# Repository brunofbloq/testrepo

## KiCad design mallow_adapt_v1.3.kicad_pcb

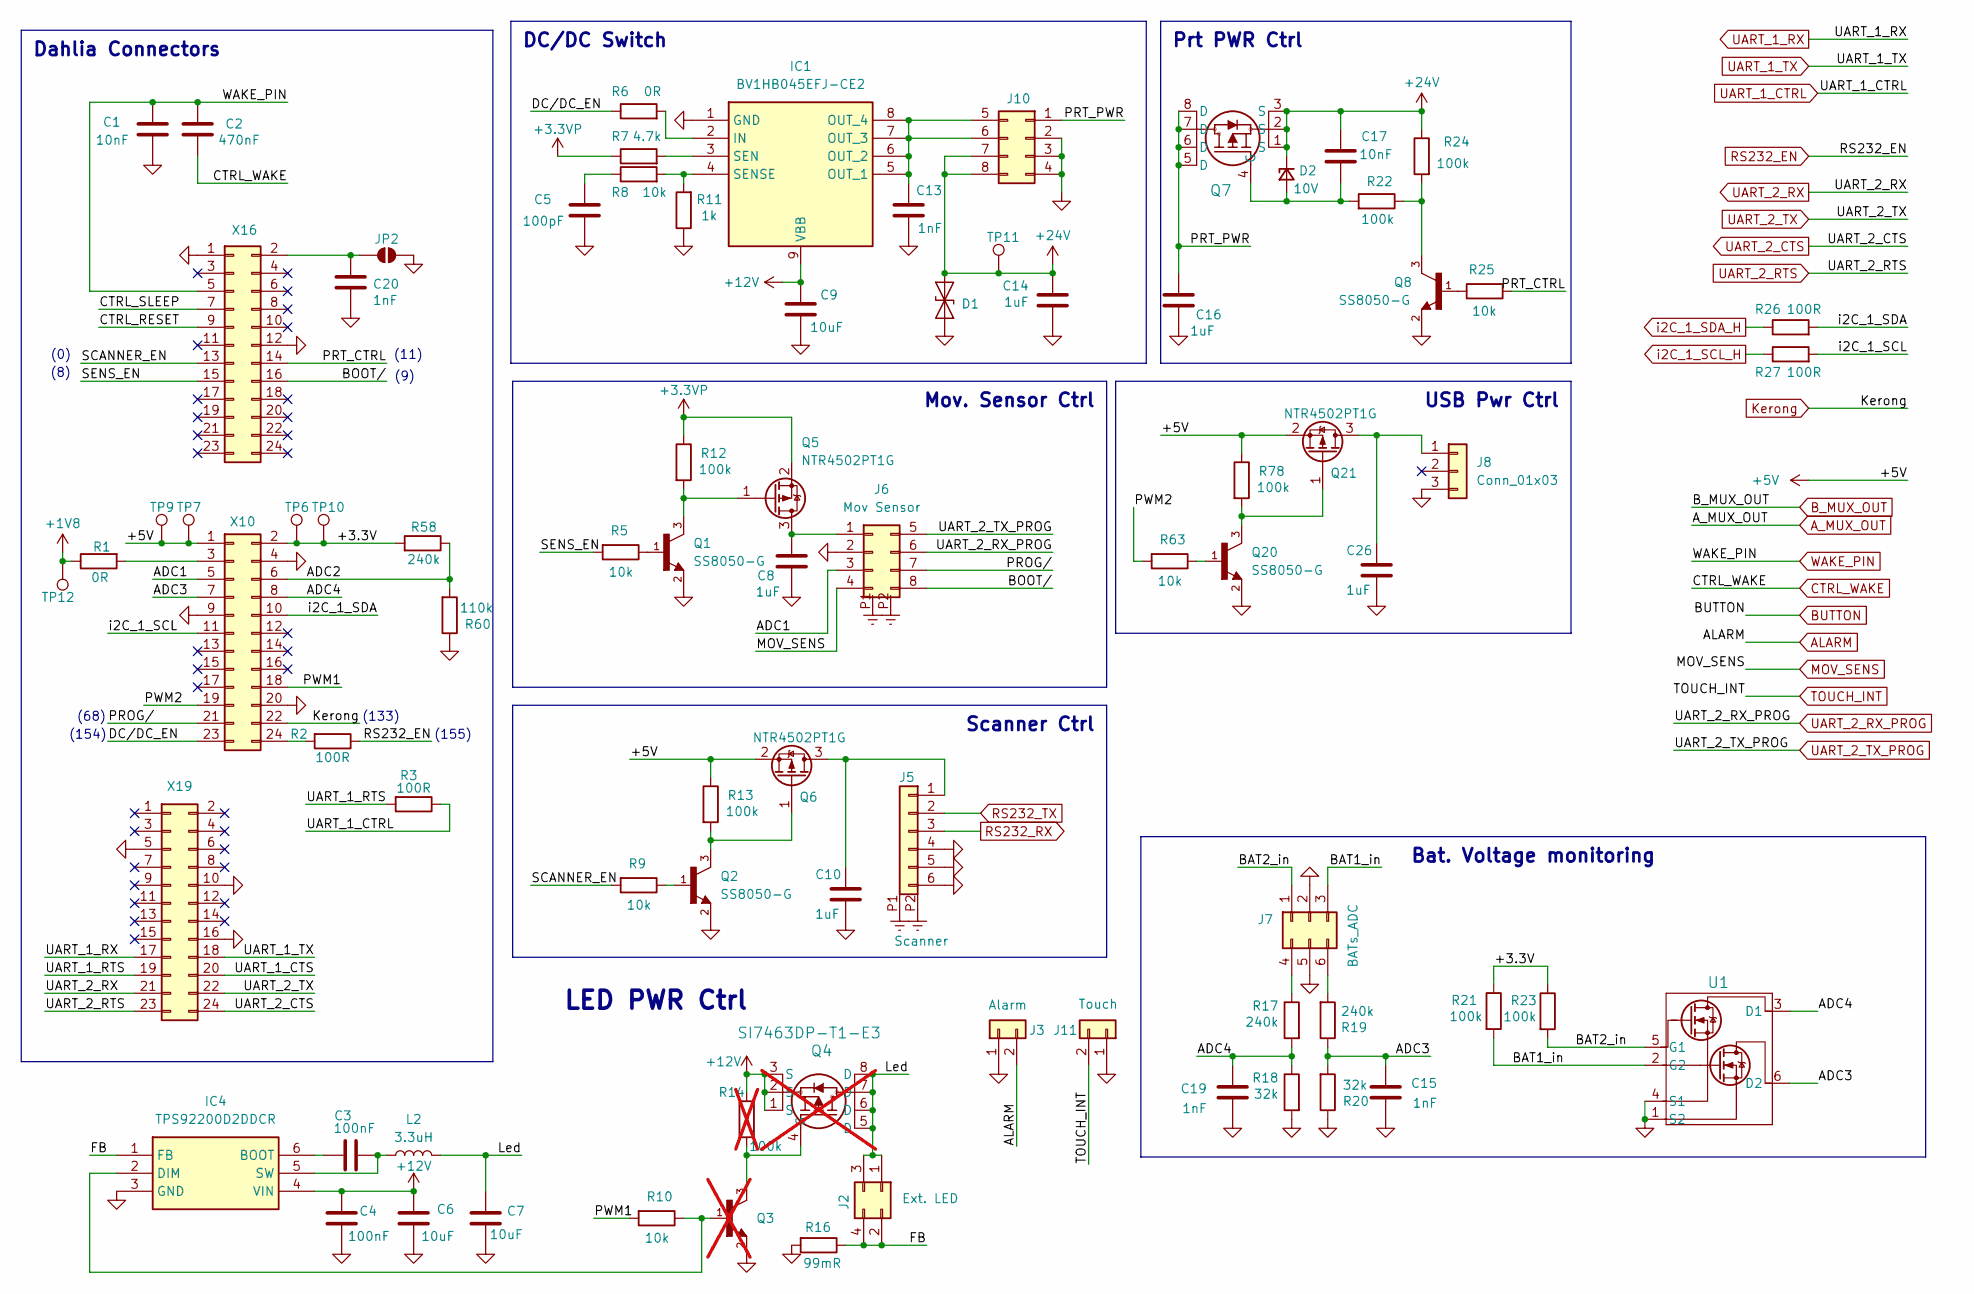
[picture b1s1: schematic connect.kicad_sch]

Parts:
C1, C17: 10nF; C_0603_1608Metric
C2: 470nF; C_0603_1608Metric
C3, C4: 100nF; C_0603_1608Metric
C5: 100pF; C_0603_1608Metric
C6, C7, C9: 10uF; C_0805_2012Metric
C8, C10, C16, C26: 1uF; C_0603_1608Metric
C13, C15, C19, C20: 1nF; C_0603_1608Metric
C14: 1uF; C_0805_2012Metric
D1: SMAJ24CA; D_SMA
D2: 10V; D_SOD-323_HandSoldering
IC1: BV1HB045EFJ-CE2; SOIC127P600X100-9N; Manufacturer_Part_Number BV1HB045EFJ-CE2
IC4: TPS92200D2DDCR; SOT95P280X110-6N; Manufacturer_Part_Number TPS92200D2DDCR
J2: Ext. LED; 1053101104
J3: Alarm; 1053091202
J5: Scanner; CON_430450624_MOL
J6: Mov Sensor; CON_1053121108
J7: BATs_ADC; CON_1053101106
J8: Conn_01x03; 1053091203
J10: 46015-0803
J11: Touch; Molex_PicoBlade_53048-0210_1x02_P1.25mm_Horizontal
JP2: Recovery; SolderJumper-2_P1.3mm_Open_RoundedPad1.0x1.5mm
L2: 3.3uH; L_1210_3225Metric
Q1, Q2, Q8, Q20: SS8050-G; TRANS_SS8050-G; PARTREV A
Q3: SS8050-G; TRANS_SS8050-G; PARTREV A; not fitted
Q4: SI7463DP-T1-E3; MOSFET_65DP-T1-E3_VIS; not fitted
Q5, Q6, Q21: NTR4502PT1G; SOT96P237X111-3N
Q7: SI7463DP-T1-E3; MOSFET_65DP-T1-E3_VIS
R1, R6: 0R; R_0603_1608Metric
R2, R3, R26, R27: 100R; R_0603_1608Metric
R5, R8, R9, R10, R25, R63: 10k; R_0603_1608Metric
R7: 4.7k; R_0603_1608Metric
R11: 1k; R_0603_1608Metric
R12, R13, R21, R22, R23, R24, R78: 100k; R_0603_1608Metric
R14: 100k; R_0603_1608Metric; not fitted
R16: 99mR; R_0805_2012Metric
R17, R19, R58: 240k; R_0603_1608Metric
R18, R20: 32k; R_0603_1608Metric
R60: 110k; R_0603_1608Metric
TP6, TP7, TP9, TP10, TP11, TP12: TestPoint; TestPoint_Pad_D2.0mm
U1: DMN53D0LDW-7; SOT-363_DIO
X10, X16, X19: Conn_02x12_Odd_Even; PinHeader_2x12_P2.54mm_Vertical

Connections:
+1V8: R1.1, TP12.1; also elsewhere on the board
+3.3VP: Q5.2 (S), R7.1, R12.1; also elsewhere on the board
+5V: Q6.2 (S), Q21.2 (S), R13.1, R78.1, TP7.1, TP9.1, X10.1
+12V: C4.1, C6.1, C9.1, IC1.9 (VBB), IC4.4 (VIN), Q4.1 (S), Q4.2 (S), Q4.3 (S), R14.1; also elsewhere on the board
+24V: C14.1, C17.1, D1.2 (A2), D2.1 (K), J10.7, J10.8, Q7.1 (S), Q7.2 (S), Q7.3 (S), R24.1, TP11.1; also elsewhere on the board
/Connectors/+3.3V: R21.1, R23.1, R58.2, TP6.1, TP10.1, X10.2
/Connectors/ADC1: J6.3, X10.5
/Connectors/ADC2: R58.1, R60.2, X10.6
/Connectors/ADC3: C15.1, R19.1, R20.2, U1.6 (D2), X10.7
/Connectors/ADC4: C19.1, R17.2, R18.1, U1.3 (D1), X10.8
/Connectors/BAT1_in: J7.3, R21.2, U1.2 (G2)
/Connectors/BAT2_in: J7.1, R23.2, U1.5 (G1)
/Connectors/BOOT/: J6.8, X16.16
/Connectors/CTRL_RESET: X16.9
/Connectors/CTRL_SLEEP: X16.7
/Connectors/DC/DC_EN: R6.1, X10.23
/Connectors/FB: IC4.1 (FB), J2.2, J2.4, R16.1
/Connectors/Led: C7.1, J2.1, J2.3, L2.2, Q4.5 (D), Q4.6 (D), Q4.7 (D), Q4.8 (D)
/Connectors/PROG/: J6.7, X10.21
/Connectors/PRT_CTRL: R25.2, X16.14
/Connectors/PRT_PWR: C16.1, J10.1, Q7.5 (D), Q7.6 (D), Q7.7 (D), Q7.8 (D)
/Connectors/PWM1: R10.2, X10.18
/Connectors/PWM2: R63.2, X10.19
/Connectors/SCANNER_EN: R9.2, X16.13
/Connectors/SENS_EN: R5.2, X16.15
/Connectors/UART_1_CTS: X19.20
/Connectors/UART_1_RTS: R3.2, X19.19
/Connectors/i2C_1_SCL: R27.2, X10.11
/Connectors/i2C_1_SDA: R26.2, X10.10
ALARM: J3.2; also elsewhere on the board
CTRL_WAKE: C2.2; also elsewhere on the board
GND: C1.2, C4.2, C5.2, C6.2, C7.2, C8.2, C9.2, C10.2, C13.2, C14.2, C15.2, C16.2, C19.2, C20.2, C26.2, D1.1 (A1), IC1.1 (GND), IC4.3 (GND), J3.1, J5.4, J5.5, J5.6, J6.2, J7.2, J7.5, J8.3, J10.2, J10.3, J10.4, J11.1, JP2.2 (B), Q1.2, Q2.2, Q3.2, Q8.2, Q20.2, R11.1, R16.2, R18.2, R20.1, R60.1, U1.1 (S2), U1.4 (S1), X10.4, X10.9, X10.20, X16.1, X16.12, X19.5, X19.10, X19.16; also elsewhere on the board
GND_CHASSIS: J5.P1 (Pin_6), J5.P2 (Pin_6), J6.P1 (Pin_8), J6.P2 (Pin_8); also elsewhere on the board
Kerong: X10.22; also elsewhere on the board
MOV_SENS: J6.4; also elsewhere on the board
unnamed: C5.1, R8.1
unnamed: C17.2, D2.2 (A), Q7.4 (G), R22.2
unnamed: IC1.2 (IN), R6.2
unnamed: C13.1, IC1.5 (OUT_1), IC1.6 (OUT_2), IC1.7 (OUT_3), IC1.8 (OUT_4), J10.5, J10.6
unnamed: IC1.3 (SEN), R7.2
unnamed: IC1.4 (SENSE), R8.2, R11.2
unnamed: C3.1, IC4.6 (BOOT)
unnamed: IC4.2 (DIM), Q3.1, R10.1
unnamed: C3.2, IC4.5 (SW), L2.1
unnamed: C10.1, J5.1, Q6.3 (D)
unnamed: C8.1, J6.1, Q5.3 (D)
unnamed: J7.4, R17.1
unnamed: J7.6, R19.2
unnamed: C26.1, J8.1, Q21.3 (D)
unnamed: C20.1, JP2.1 (A), X16.2
unnamed: Q1.1, R5.1
unnamed: Q2.1, R9.1
unnamed: Q3.3, Q4.4 (G), R14.2
unnamed: Q1.3, Q5.1 (G), R12.2
unnamed: Q2.3, Q6.1 (G), R13.2
unnamed: Q8.1, R25.1
unnamed: Q8.3, R22.1, R24.2
unnamed: Q20.1, R63.1
unnamed: Q20.3, Q21.1 (G), R78.2
unnamed: R1.2, X10.3
unnamed: R2.2, X10.24
RS232_EN: R2.1; also elsewhere on the board
RS232_RX: J5.3; also elsewhere on the board
RS232_TX: J5.2; also elsewhere on the board
TOUCH_INT: J11.2; also elsewhere on the board
UART_1_CTRL: R3.1; also elsewhere on the board
UART_1_RX: X19.17; also elsewhere on the board
UART_1_TX: X19.18; also elsewhere on the board
UART_2_CTS: X19.24; also elsewhere on the board
UART_2_RTS: X19.23; also elsewhere on the board
UART_2_RX: X19.21; also elsewhere on the board
UART_2_RX_PROG: J6.6; also elsewhere on the board
UART_2_TX: X19.22; also elsewhere on the board
UART_2_TX_PROG: J6.5; also elsewhere on the board
WAKE_PIN: C1.1, C2.1, X16.5; also elsewhere on the board
i2C_1_SCL_H: R27.1; also elsewhere on the board
i2C_1_SDA_H: R26.1; also elsewhere on the board

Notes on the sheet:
USB Pwr Ctrl
Dahlia Connectors
LED PWR Ctrl
Bat. Voltage monitoring
Scanner Ctrl
DC/DC Switch
Mov. Sensor Ctrl
Prt PWR Ctrl
(0)
(8)
(9)
(133)
(68)
(154)
(11)
(155)

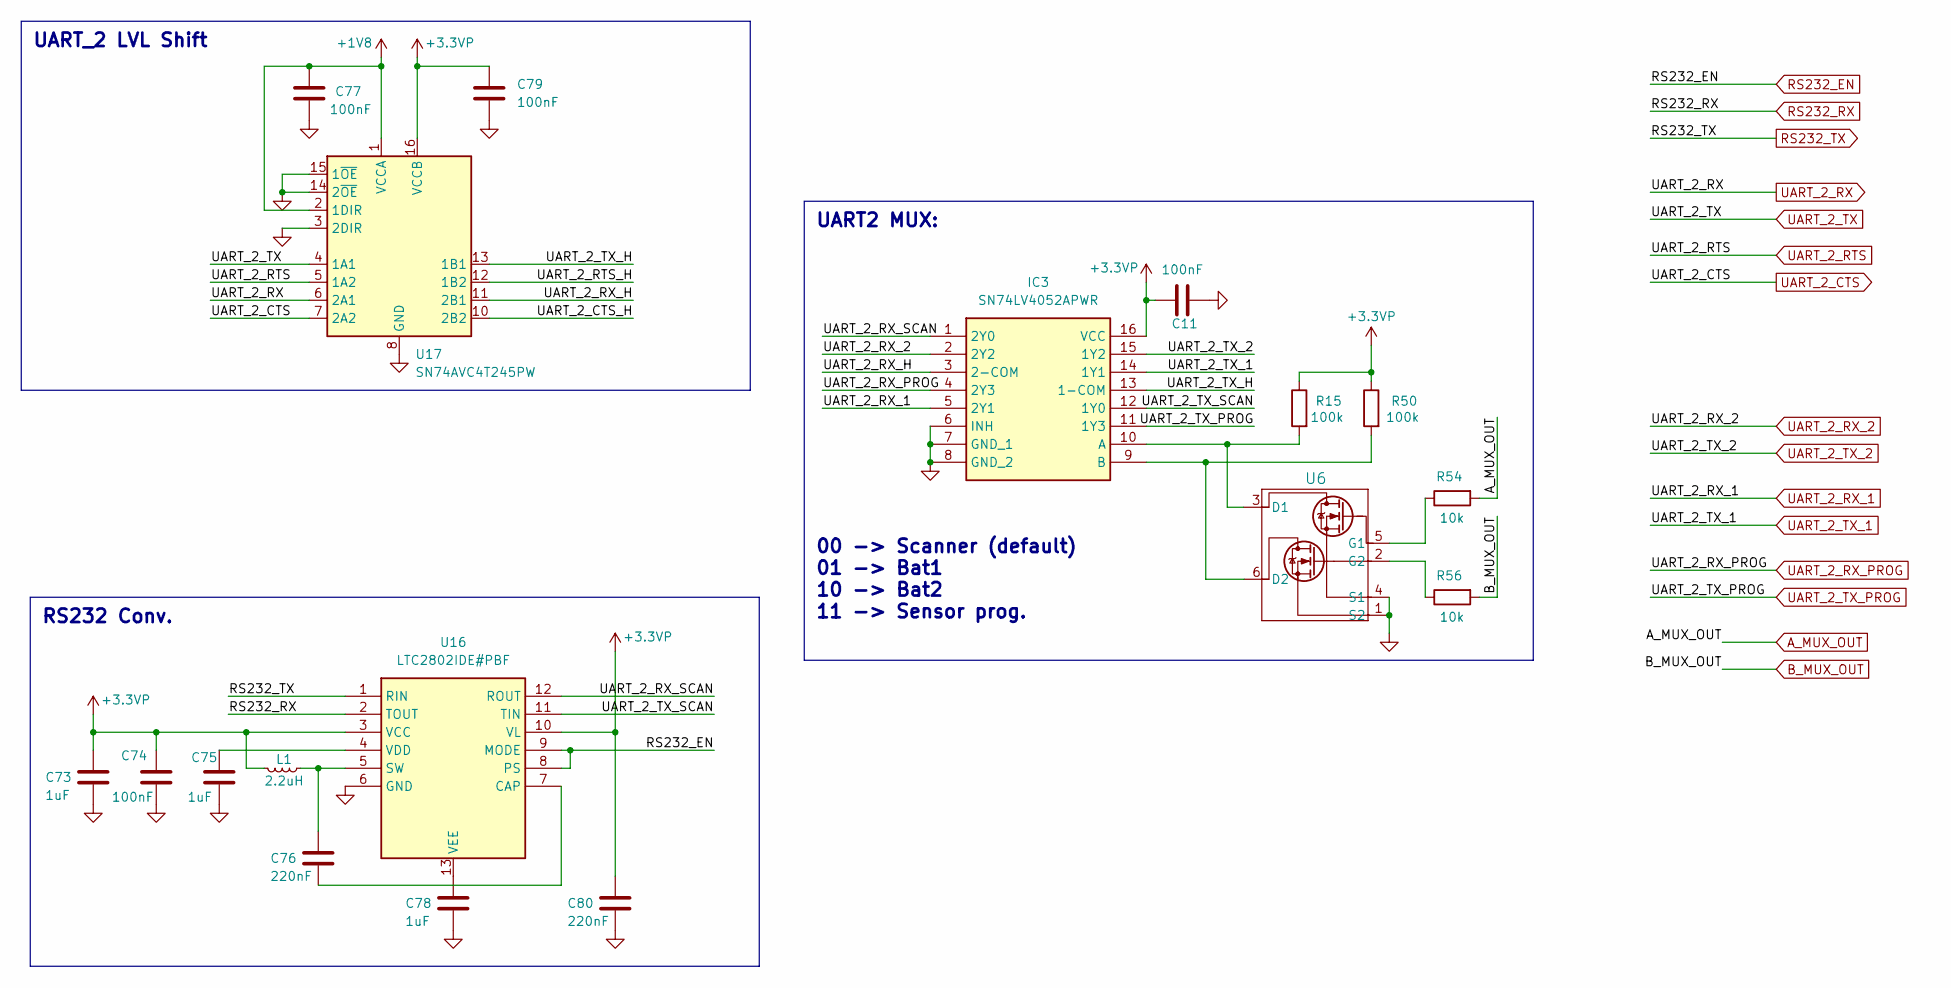
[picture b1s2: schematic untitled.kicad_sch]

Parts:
C11, C74, C77, C79: 100nF; C_0603_1608Metric
C73, C75, C78: 1uF; C_0603_1608Metric
C76, C80: 220nF; C_0603_1608Metric
IC3: SN74LV4052APWR; SOP65P640X120-16N; Manufacturer_Part_Number SN74LV4052APWR; Mouser Part Number 595-SN74LV4052APWR
L1: 2.2uH; L_0805_2012Metric
R15, R50: 100k; R_0603_1608Metric
R54, R56: 10k; R_0603_1608Metric
U6: DMN53D0LDW-7; SOT-363_DIO
U16: LTC2802IDE#PBF; LTC2802__SON50P300X400X80-13N-D; Manufacturer_Part_Number LTC2802IDE#PBF; Mouser Part Number 584-LTC2802IDE#PBF
U17: SN74AVC4T245PW; TSSOP-16_4.4x5mm_P0.65mm

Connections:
+1V8: C77.1, U17.1 (VCCA), U17.2 (1DIR); also elsewhere on the board
+3.3VP: C11.1, C73.1, C74.1, C79.1, C80.1, IC3.16 (VCC), L1.2, R15.1, R50.1, U16.3 (VCC), U16.10 (VL), U17.16 (VCCB); also elsewhere on the board
/UARTs/UART_2_CTS_H: U17.10 (2B2)
/UARTs/UART_2_RTS_H: U17.12 (1B2)
/UARTs/UART_2_RX_H: IC3.3 (2-COM), U17.11 (2B1)
/UARTs/UART_2_RX_SCAN: IC3.1 (2Y0), U16.12 (ROUT)
/UARTs/UART_2_TX_H: IC3.13 (1-COM), U17.13 (1B1)
/UARTs/UART_2_TX_SCAN: IC3.12 (1Y0), U16.11 (TIN)
A_MUX_OUT: R54.2; also elsewhere on the board
B_MUX_OUT: R56.2; also elsewhere on the board
GND: C11.2, C73.2, C74.2, C75.2, C77.2, C78.2, C79.2, C80.2, IC3.6 (INH), IC3.7 (GND_1), IC3.8 (GND_2), U6.1 (S2), U6.4 (S1), U16.6 (GND), U17.3 (2DIR), U17.8 (GND), U17.9 (GND), U17.14 (2~OE), U17.15 (1~OE); also elsewhere on the board
unnamed: IC3.10 (A), R15.2, U6.3 (D1)
unnamed: IC3.9 (B), R50.2, U6.6 (D2)
unnamed: R54.1, U6.5 (G1)
unnamed: R56.1, U6.2 (G2)
unnamed: C76.2, U16.7 (CAP)
unnamed: C76.1, L1.1, U16.5 (SW)
unnamed: C75.1, U16.4 (VDD)
unnamed: C78.1, U16.13 (VEE)
RS232_EN: U16.8 (PS), U16.9 (MODE); also elsewhere on the board
RS232_RX: U16.2 (TOUT); also elsewhere on the board
RS232_TX: U16.1 (RIN); also elsewhere on the board
UART_2_CTS: U17.7 (2A2); also elsewhere on the board
UART_2_RTS: U17.5 (1A2); also elsewhere on the board
UART_2_RX: U17.6 (2A1); also elsewhere on the board
UART_2_RX_1: IC3.5 (2Y1); also elsewhere on the board
UART_2_RX_2: IC3.2 (2Y2); also elsewhere on the board
UART_2_RX_PROG: IC3.4 (2Y3); also elsewhere on the board
UART_2_TX: U17.4 (1A1); also elsewhere on the board
UART_2_TX_1: IC3.14 (1Y1); also elsewhere on the board
UART_2_TX_2: IC3.15 (1Y2); also elsewhere on the board
UART_2_TX_PROG: IC3.11 (1Y3); also elsewhere on the board

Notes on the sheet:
UART_2 LVL Shift
RS232 Conv.
UART2 MUX: 00 -> Scanner (default) 01 -> Bat1 10 -> Bat2 11 -> Sensor prog.

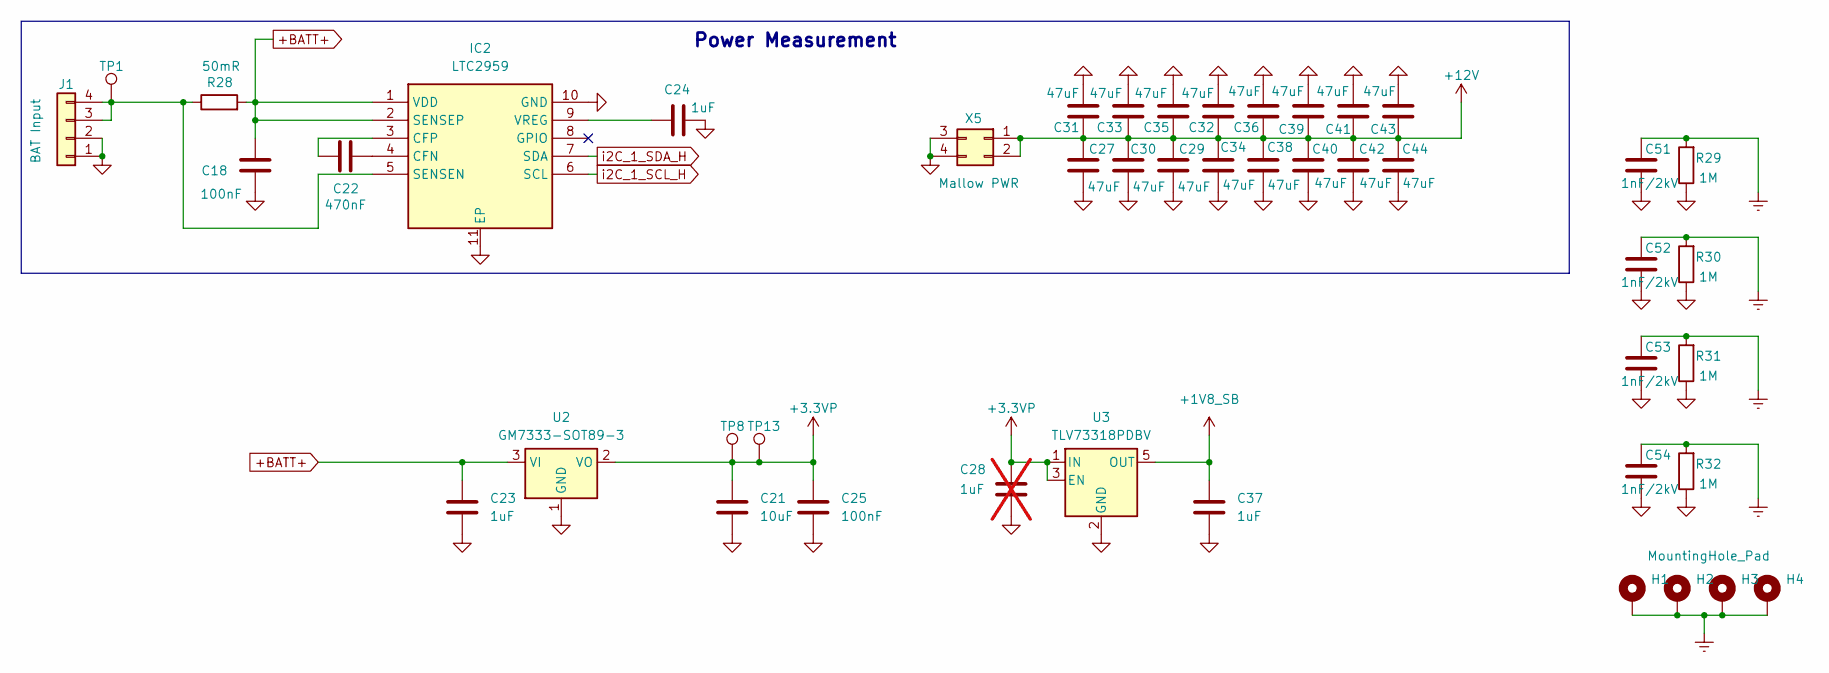
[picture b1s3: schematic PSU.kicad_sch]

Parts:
C18, C25: 100nF; C_0603_1608Metric
C21: 10uF; C_0603_1608Metric
C22: 470nF; C_0603_1608Metric
C23, C24, C37: 1uF; C_0603_1608Metric
C27, C29, C30, C31, C32, C33, C34, C35, C36, C38, C39, C40, C41, C42, C43, C44: 47uF; C_1210_3225Metric
C28: 1uF; C_0603_1608Metric; not fitted
C51, C52, C53, C54: 1nF/2kV; C_1206_3216Metric
H1, H2, H3, H4: MountingHole_Pad; MountingHole_3.2mm_M3_ISO7380_Pad_TopBottom
IC2: LTC2959; SON50P200X300X80-11N-D; Manufacturer_Part_Number LTC2959; Mouser Part Number N/A
J1: BAT Input; 46015-0403
R28: 50mR; R_2512_6332Metric
R29, R30, R31, R32: 1M; R_1206_3216Metric
TP1, TP8, TP13: TestPoint; TestPoint_Pad_D2.0mm
U2: GM7333-SOT89-3; SOT-89-3
U3: TLV73318PDBV; SOT-23-5
X5: Mallow PWR; PinHeader_2x02_P2.54mm_Vertical

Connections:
+1V8_SB: C37.1, U3.5 (OUT); also elsewhere on the board
+3.3VP: C21.1, C25.1, C28.1, TP8.1, TP13.1, U2.2 (VO), U3.1 (IN), U3.3 (EN); also elsewhere on the board
+12V: C27.1, C29.1, C30.1, C31.1, C32.1, C33.1, C34.1, C35.1, C36.1, C38.1, C39.1, C40.1, C41.1, C42.1, C43.1, C44.1, X5.1, X5.2; also elsewhere on the board
+BATT+: C18.1, C23.1, IC2.1 (VDD), IC2.2 (SENSEP), R28.2, U2.3 (VI); also elsewhere on the board
GND: C18.2, C21.2, C23.2, C24.2, C25.2, C27.2, C28.2, C29.2, C30.2, C31.2, C32.2, C33.2, C34.2, C35.2, C36.2, C37.2, C38.2, C39.2, C40.2, C41.2, C42.2, C43.2, C44.2, C51.2, C52.2, C53.2, C54.2, IC2.10 (GND), IC2.11 (EP), J1.1, J1.2, R29.1, R30.1, R31.1, R32.1, U2.1 (GND), U3.2 (GND), X5.3, X5.4; also elsewhere on the board
GND_CHASSIS: C51.1, C52.1, C53.1, C54.1, H1.1, H2.1, H3.1, H4.1, R29.2, R30.2, R31.2, R32.2; also elsewhere on the board
unnamed: C22.2, IC2.4 (CFN)
unnamed: C22.1, IC2.3 (CFP)
unnamed: IC2.5 (SENSEN), J1.3, J1.4, R28.1, TP1.1
unnamed: C24.1, IC2.9 (VREG)
i2C_1_SCL_H: IC2.6 (SCL); also elsewhere on the board
i2C_1_SDA_H: IC2.7 (SDA); also elsewhere on the board

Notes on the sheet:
Power Measurement

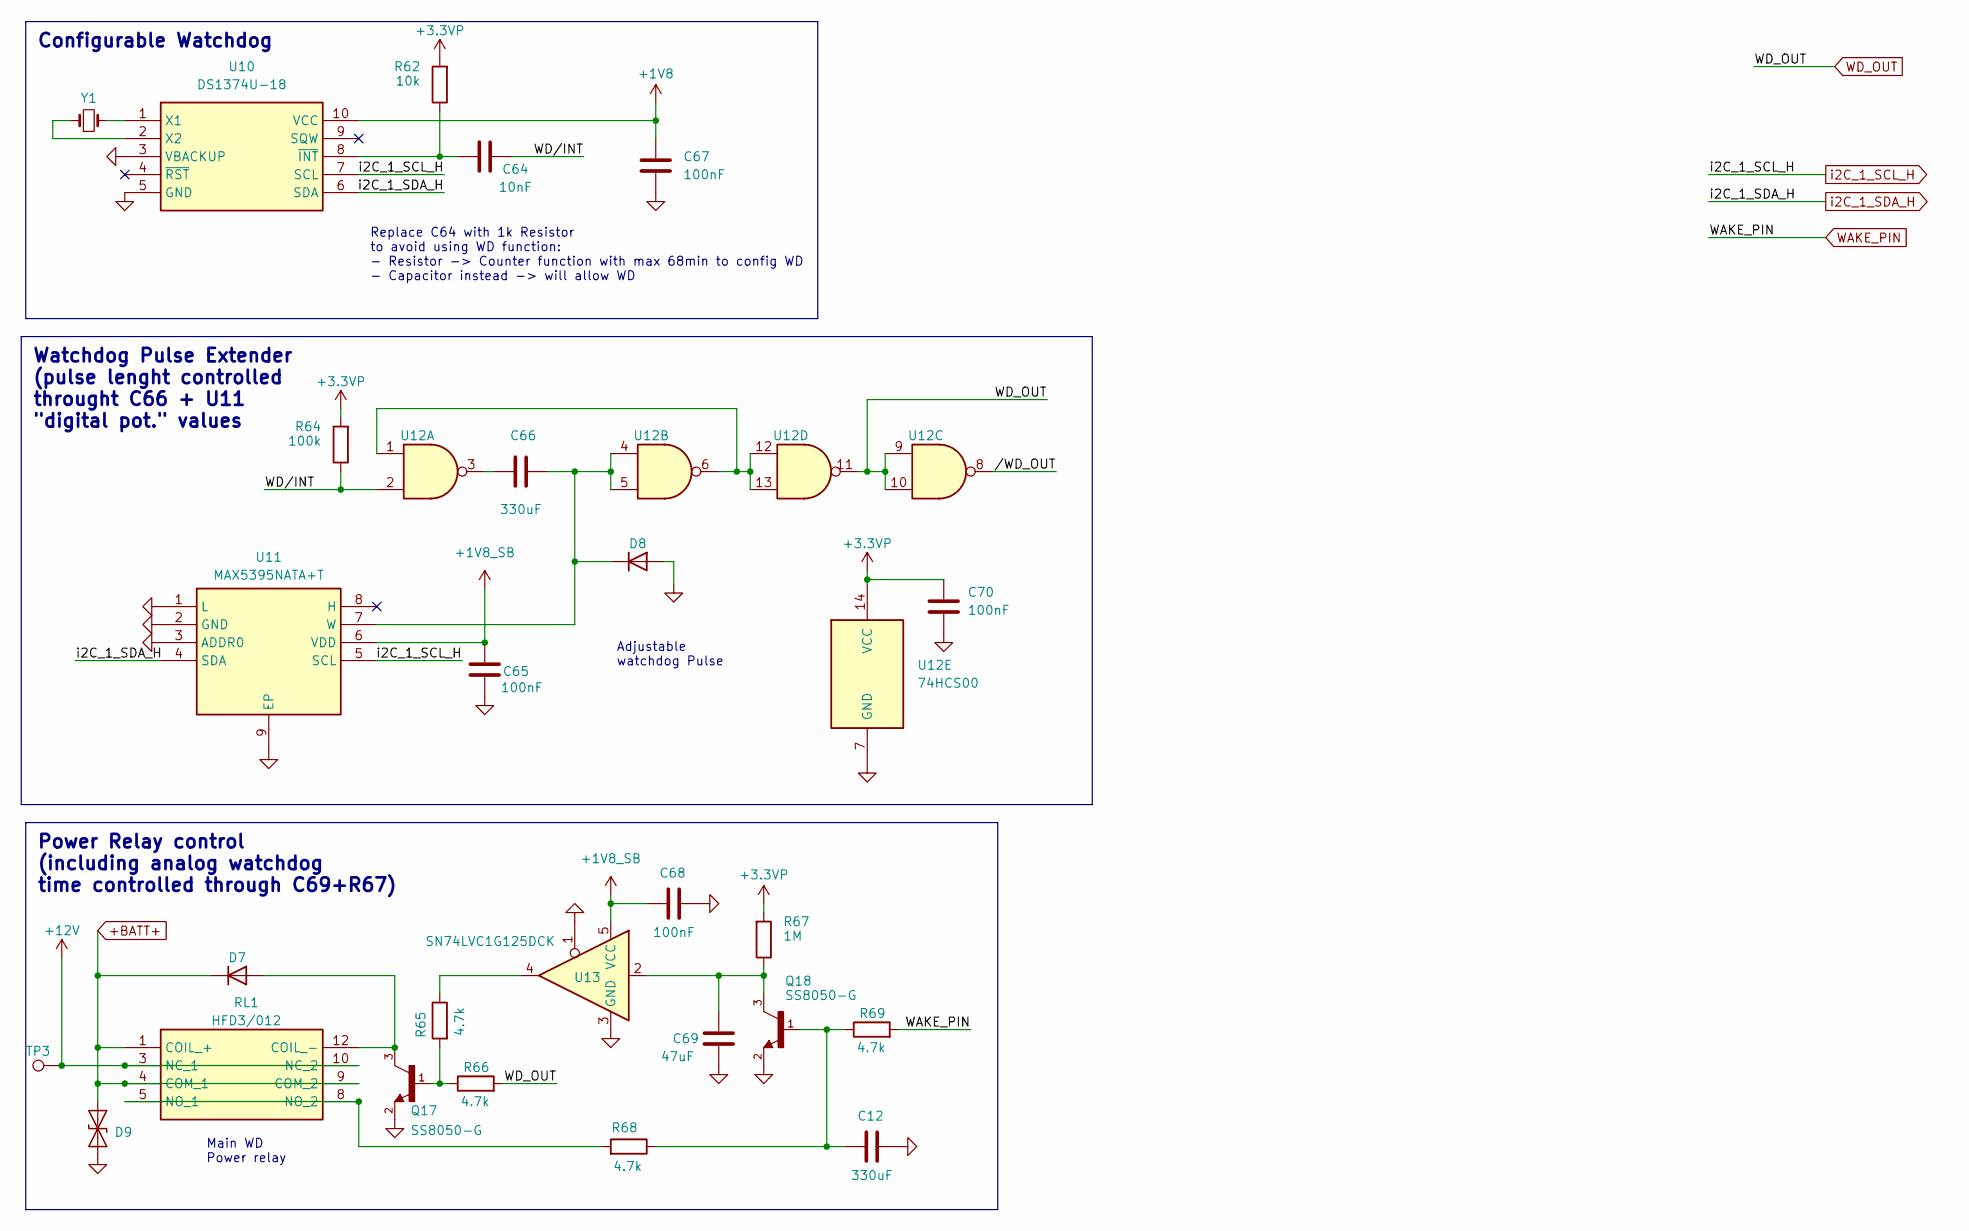
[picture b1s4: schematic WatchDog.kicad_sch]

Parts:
C12, C66: 330uF; C_1210_3225Metric
C64: 10nF; C_0603_1608Metric
C65, C67, C68, C70: 100nF; C_0603_1608Metric
C69: 47uF; C_0603_1608Metric
D7, D8: 1n4148W; D_SOD-123
D9: SMAJ14CA; D_SMA
Q17, Q18: SS8050-G; TRANS_SS8050-G; PARTREV A
R62: 10k; R_0603_1608Metric
R64: 100k; R_0603_1608Metric
R65, R66, R68, R69: 4.7k; R_0603_1608Metric
R67: 1M; R_0603_1608Metric
RL1: HFD3/012; TX2SA12V; Manufacturer_Part_Number TX2SA-12V; Mouser Part Number 769-TX2SA-12V
TP3: TestPoint; TestPoint_Pad_D2.0mm
U10: DS1374U-18; SOP50P490X110-10N; Manufacturer_Part_Number DS1374U-3+; Mouser Part Number 700-DS1374U-3
U11: MAX5395NATA+T; MAX5393__SON50P200X200X80-9N-D; Manufacturer_Part_Number MAX5395NATA+T; Mouser Part Number 700-MAX5395NATA+T
U12: 74HCS00; TSSOP-14_4.4x5mm_P0.65mm
U13: SN74LVC1G125DCK; Texas_R-PDSO-G5_DCK-5
Y1: Crystal_Small; Crystal_SMD_3215-2Pin_3.2x1.5mm

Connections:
+1V8: C67.1, U10.10 (VCC); also elsewhere on the board
+1V8_SB: C65.1, C68.1, U11.6 (VDD), U13.5 (VCC); also elsewhere on the board
+3.3VP: C70.1, R62.2, R64.2, R67.2, U12.14 (VCC); also elsewhere on the board
+12V: RL1.3 (NC_1), RL1.10 (NC_2), TP3.1; also elsewhere on the board
+BATT+: D7.1 (K), D9.2 (A2), RL1.1 (COIL_+), RL1.4 (COM_1), RL1.9 (COM_2); also elsewhere on the board
/Watchdog/WD/INT: C64.2, R64.1, U12.2
/Watchdog//WD_OUT: U12.8
GND: C12.2, C65.2, C67.2, C68.2, C69.2, C70.2, D8.2 (A), D9.1 (A1), Q17.2, Q18.2, U10.3 (VBACKUP), U10.5 (GND), U11.1 (L), U11.2 (GND), U11.3 (ADDR0), U11.9 (EP), U12.7 (GND), U13.1, U13.3 (GND); also elsewhere on the board
unnamed: C12.1, Q18.1, R68.1, R69.1
unnamed: C66.1, U12.3
unnamed: C69.1, Q18.3, R67.1, U13.2
unnamed: D7.2 (A), Q17.3, RL1.12 (COIL_-)
unnamed: C66.2, D8.1 (K), U11.7 (W), U12.4, U12.5
unnamed: Q17.1, R65.2, R66.1
unnamed: R65.1, U13.4
unnamed: R68.2, RL1.5 (NO_1), RL1.8 (NO_2)
unnamed: U10.1 (X1), Y1.2
unnamed: U10.2 (X2), Y1.1
unnamed: C64.1, R62.1, U10.8 (~INT)
unnamed: U12.1, U12.6, U12.12, U12.13
WAKE_PIN: R69.2; also elsewhere on the board
WD_OUT: R66.2, U12.9, U12.10, U12.11
i2C_1_SCL_H: U10.7 (SCL), U11.5 (SCL); also elsewhere on the board
i2C_1_SDA_H: U10.6 (SDA), U11.4 (SDA); also elsewhere on the board

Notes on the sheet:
Watchdog Pulse Extender (pulse lenght controlled throught C66 + U11 "digital pot." values
Power Relay control (including analog watchdog time controlled through C69+R67)
Configurable Watchdog
Main WD Power relay
Adjustable watchdog Pulse
Replace C64 with 1k Resistor to avoid using WD function: - Resistor -> Counter function with max 68min to config WD - Capacitor instead -> will allow WD

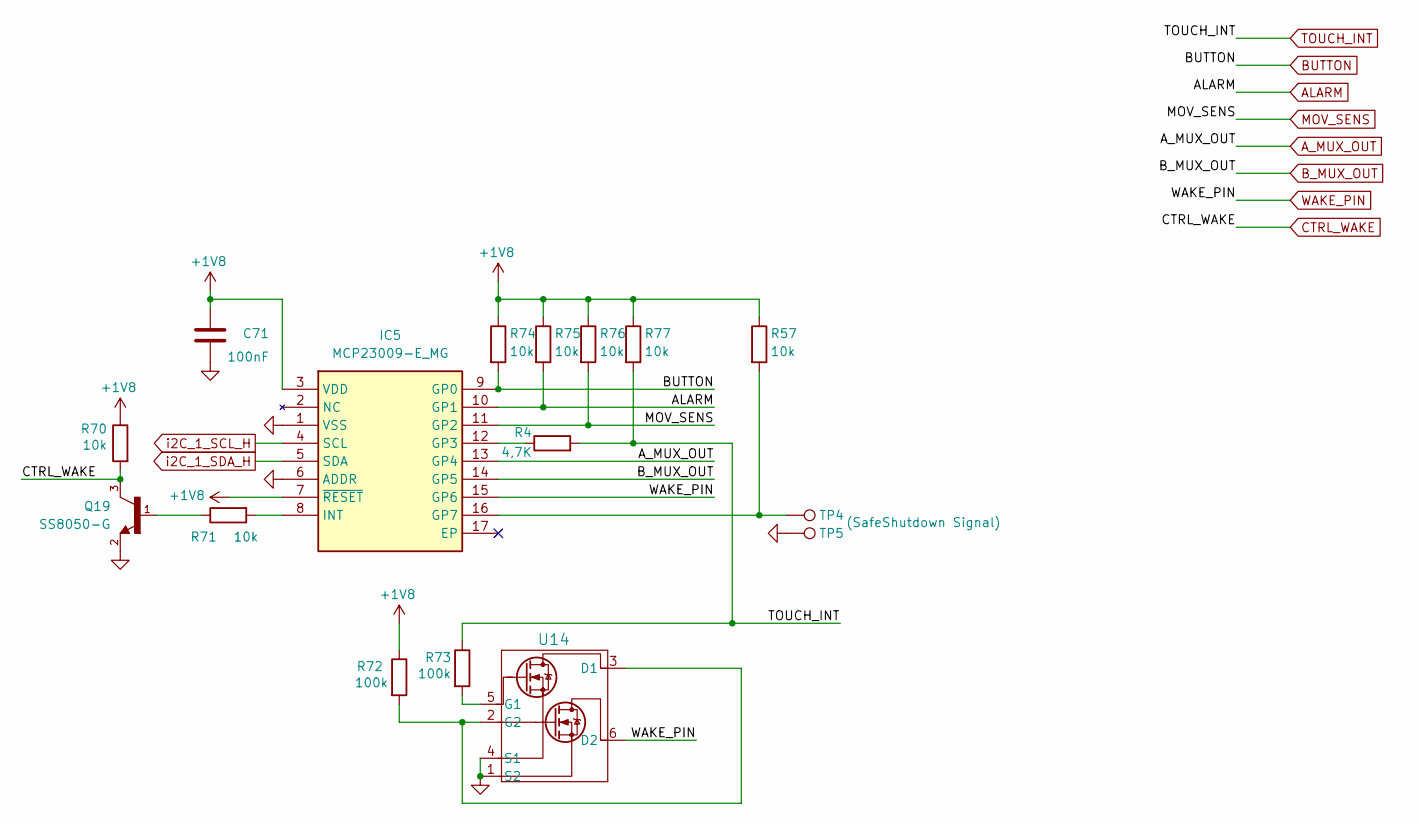
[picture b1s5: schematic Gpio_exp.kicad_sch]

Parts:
C71: 100nF; C_0603_1608Metric
IC5: MCP23009-E_MG; QFN50P300X300X90-17N-D; Manufacturer_Part_Number MCP23009-E/MG; Mouser Part Number 579-MCP23009-E/MG
Q19: SS8050-G; TRANS_SS8050-G; PARTREV A
R4: 4,7K; R_0603_1608Metric
R57, R70, R71, R74, R75, R76, R77: 10k; R_0603_1608Metric
R72, R73: 100k; R_0603_1608Metric
TP4: (SafeShutdown Signal); TestPoint_Pad_D2.0mm
TP5: TestPoint; TestPoint_Pad_D2.0mm
U14: DMN53D0LDW-7; SOT-363_DIO

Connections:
+1V8: C71.1, IC5.3 (VDD), IC5.7 (~RESET), R57.1, R70.1, R72.1, R74.1, R75.1, R76.1, R77.1; also elsewhere on the board
ALARM: IC5.10 (GP1), R75.2; also elsewhere on the board
A_MUX_OUT: IC5.13 (GP4); also elsewhere on the board
BUTTON: IC5.9 (GP0), R74.2
B_MUX_OUT: IC5.14 (GP5); also elsewhere on the board
CTRL_WAKE: Q19.3, R70.2; also elsewhere on the board
GND: C71.2, IC5.1 (VSS), IC5.6 (ADDR), Q19.2, TP5.1, U14.1 (S2), U14.4 (S1); also elsewhere on the board
MOV_SENS: IC5.11 (GP2), R76.2; also elsewhere on the board
unnamed: IC5.12 (GP3), R4.1
unnamed: IC5.16 (GP7), R57.2, TP4.1
unnamed: IC5.8 (INT), R71.2
unnamed: Q19.1, R71.1
unnamed: R72.2, U14.2 (G2), U14.3 (D1)
unnamed: R73.2, U14.5 (G1)
TOUCH_INT: R4.2, R73.1, R77.2; also elsewhere on the board
WAKE_PIN: IC5.15 (GP6), U14.6 (D2); also elsewhere on the board
i2C_1_SCL_H: IC5.4 (SCL); also elsewhere on the board
i2C_1_SDA_H: IC5.5 (SDA); also elsewhere on the board

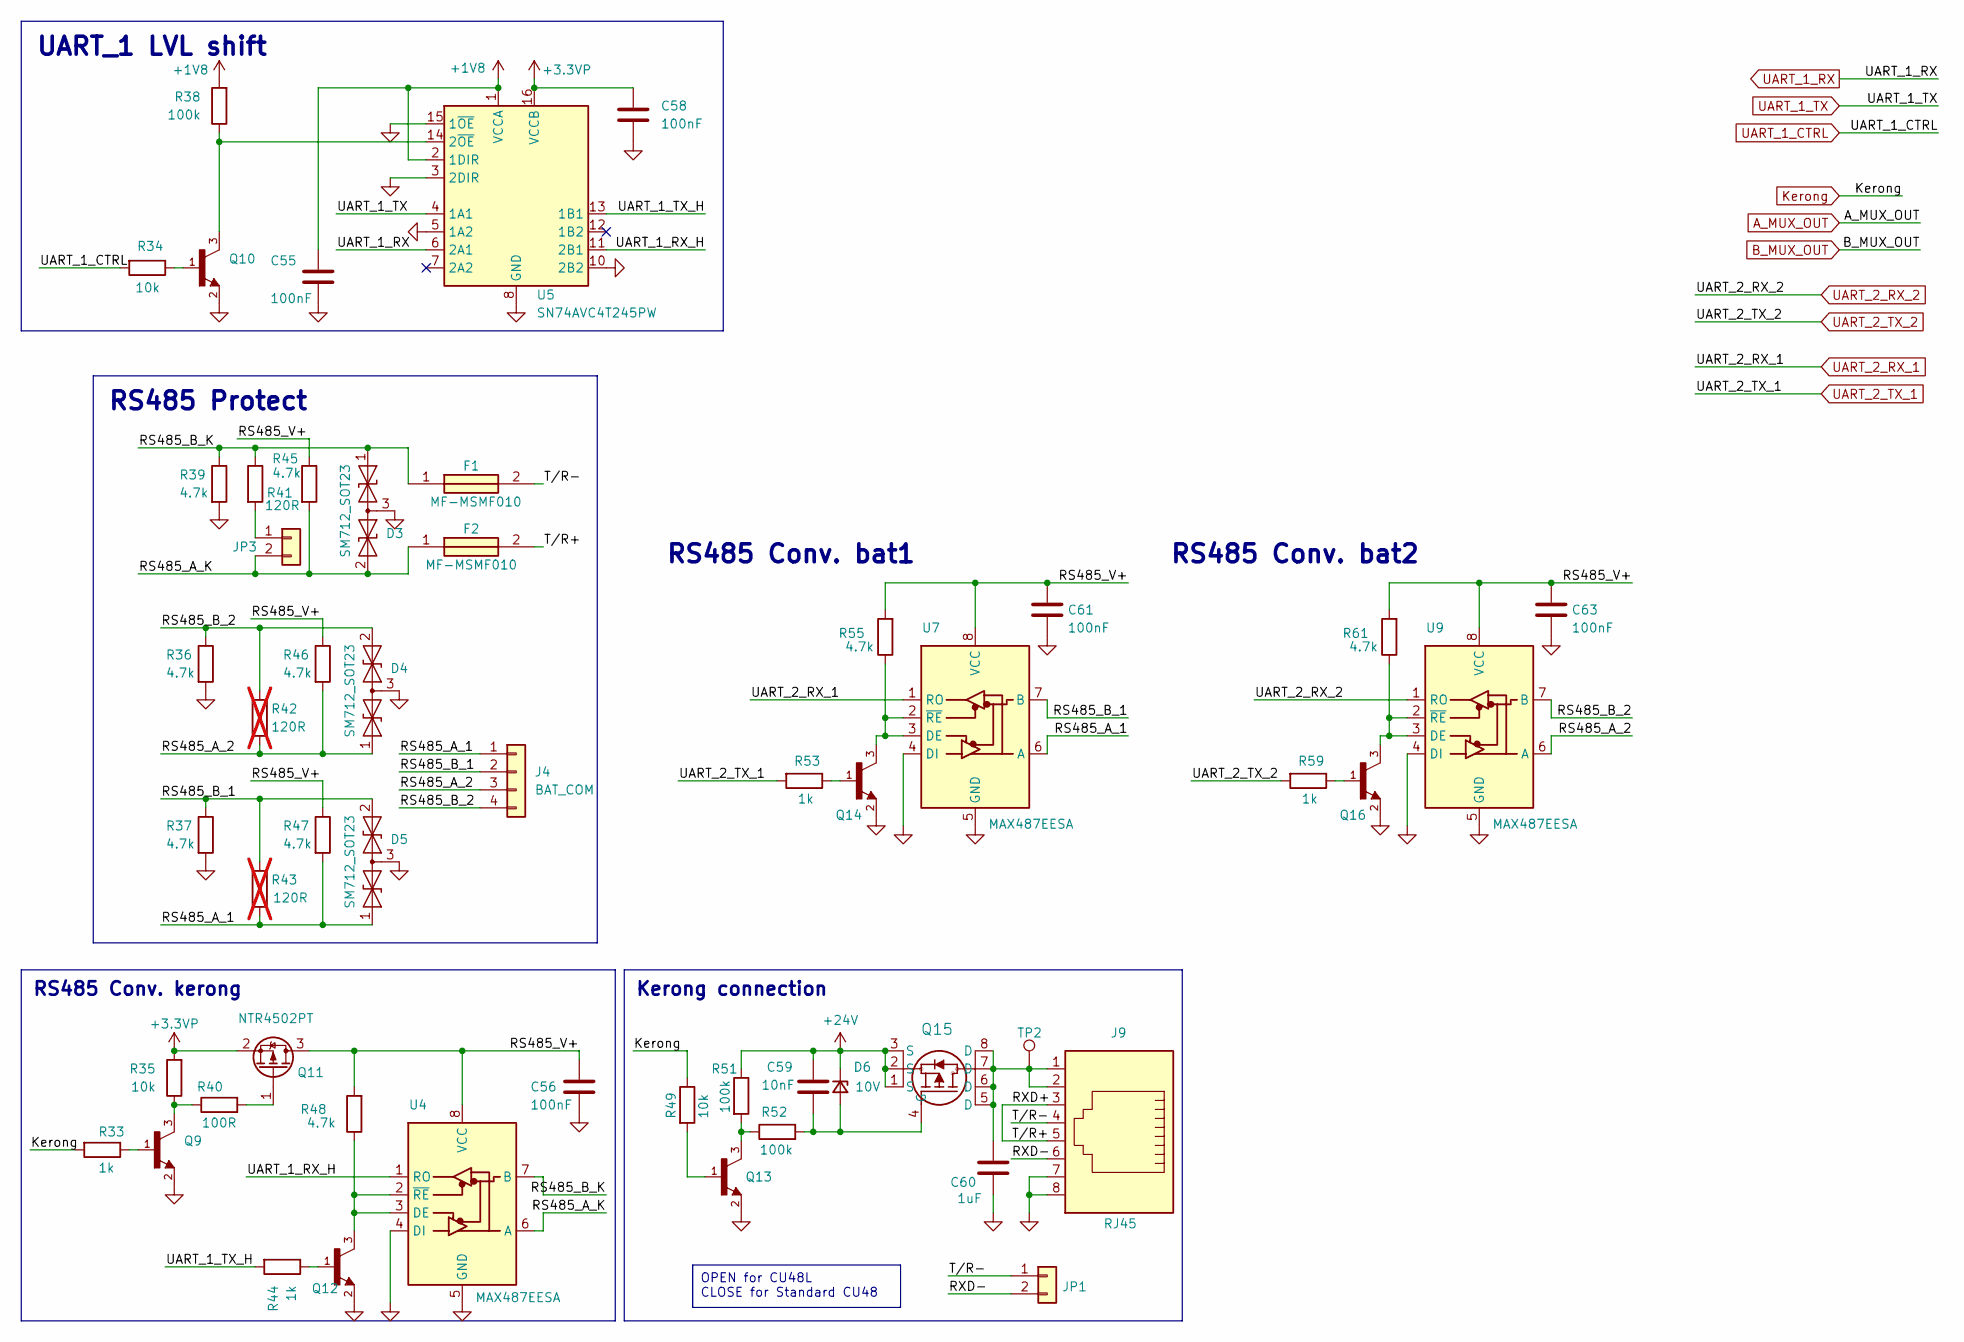
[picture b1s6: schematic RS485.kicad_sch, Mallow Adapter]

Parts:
C55, C56, C58, C61, C63: 100nF; C_0603_1608Metric
C59: 10nF; C_0603_1608Metric
C60: 1uF; C_0603_1608Metric
D3, D4, D5: SM712_SOT23; SOT-23
D6: 10V; D_SOD-323_HandSoldering
F1, F2: MF-MSMF010; FUSC4632X110N; Manufacturer_Part_Number MF-MSMF010
J4: BAT_COM; 1053091104
J9: RJ45; RJ45_OST_PJ012-8P8CX_Vertical
JP1, JP3: Conn_01x02; PinHeader_1x02_P2.54mm_Vertical
Q9, Q10, Q12, Q13, Q14, Q16: SS8050-G; TRANS_SS8050-G; PARTREV A
Q11: NTR4502PT; SOT96P237X111-3N
Q15: SI7463DP-T1-E3; MOSFET_65DP-T1-E3_VIS
R33, R44, R53, R59: 1k; R_0603_1608Metric
R34, R35, R49: 10k; R_0603_1608Metric
R36, R37, R39, R45, R46, R47, R48, R55, R61: 4.7k; R_0603_1608Metric
R38, R51, R52: 100k; R_0603_1608Metric
R40: 100R; R_0603_1608Metric
R41: 120R; R_0603_1608Metric
R42, R43: 120R; R_0603_1608Metric; not fitted
TP2: TestPoint; TestPoint_Pad_D2.0mm
U4, U7, U9: MAX487EESA; SOIC-8_3.9x4.9mm_P1.27mm
U5: SN74AVC4T245PW; TSSOP-16_4.4x5mm_P0.65mm

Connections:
+1V8: C55.1, R38.2, U5.1 (VCCA), U5.2 (1DIR); also elsewhere on the board
+3.3VP: C58.1, Q11.2 (S), R35.2, U5.16 (VCCB); also elsewhere on the board
+24V: C59.1, D6.1 (K), Q15.1 (S), Q15.2 (S), Q15.3 (S), R51.1; also elsewhere on the board
/Rs485/RS485_A_1: D5.1 (A1), J4.1, R43.2, R47.2, U7.6 (A)
/Rs485/RS485_A_2: D4.1 (A1), J4.3, R42.2, R46.2, U9.6 (A)
/Rs485/RS485_A_K: D3.2 (A2), F2.1, JP3.2, R45.2, U4.6 (A)
/Rs485/RS485_B_1: D5.2 (A2), J4.2, R37.1, R43.1, U7.7 (B)
/Rs485/RS485_B_2: D4.2 (A2), J4.4, R36.1, R42.1, U9.7 (B)
/Rs485/RS485_B_K: D3.1 (A1), F1.1, R39.1, R41.1, U4.7 (B)
/Rs485/RS485_V+: C56.1, C61.1, C63.1, Q11.3 (D), R45.1, R46.1, R47.1, R48.2, R55.2, R61.2, U4.8 (VCC), U7.8 (VCC), U9.8 (VCC)
/Rs485/RXD+: F2.2, J9.3, J9.5
/Rs485/RXD-: J9.6, JP1.2
/Rs485/T/R-: F1.2, J9.4, JP1.1
/Rs485/UART_1_RX_H: U4.1 (RO), U5.11 (2B1)
/Rs485/UART_1_TX_H: R44.2, U5.13 (1B1)
GND: C55.2, C56.2, C58.2, C60.2, C61.2, C63.2, D3.3 (common), D4.3 (common), D5.3 (common), J9.7, J9.8, Q9.2, Q10.2, Q12.2, Q13.2, Q14.2, Q16.2, R36.2, R37.2, R39.2, U4.4 (DI), U4.5 (GND), U5.3 (2DIR), U5.5 (1A2), U5.8 (GND), U5.9 (GND), U5.10 (2B2), U5.15 (1~OE), U7.4 (DI), U7.5 (GND), U9.4 (DI), U9.5 (GND); also elsewhere on the board
Kerong: R33.2, R49.1; also elsewhere on the board
unnamed: C60.1, J9.1, J9.2, Q15.5 (D), Q15.6 (D), Q15.7 (D), Q15.8 (D), TP2.1
unnamed: C59.2, D6.2 (A), Q15.4 (G), R52.2
unnamed: JP3.1, R41.2
unnamed: Q9.1, R33.1
unnamed: Q9.3, R35.1, R40.1
unnamed: Q10.1, R34.1
unnamed: Q11.1 (G), R40.2
unnamed: Q12.1, R44.1
unnamed: Q13.1, R49.2
unnamed: Q13.3, R51.2, R52.1
unnamed: Q14.1, R53.1
unnamed: Q16.1, R59.1
unnamed: Q12.3, R48.1, U4.2 (~RE), U4.3 (DE)
unnamed: Q10.3, R38.1, U5.14 (2~OE)
unnamed: Q14.3, R55.1, U7.2 (~RE), U7.3 (DE)
unnamed: Q16.3, R61.1, U9.2 (~RE), U9.3 (DE)
UART_1_CTRL: R34.2; also elsewhere on the board
UART_1_RX: U5.6 (2A1); also elsewhere on the board
UART_1_TX: U5.4 (1A1); also elsewhere on the board
UART_2_RX_1: U7.1 (RO); also elsewhere on the board
UART_2_RX_2: U9.1 (RO); also elsewhere on the board
UART_2_TX_1: R53.2; also elsewhere on the board
UART_2_TX_2: R59.2; also elsewhere on the board

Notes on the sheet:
UART_1 LVL shift
OPEN for CU48L CLOSE for Standard CU48
RS485 Conv. kerong
RS485 Conv. bat1
RS485 Protect
Kerong connection
RS485 Conv. bat2
